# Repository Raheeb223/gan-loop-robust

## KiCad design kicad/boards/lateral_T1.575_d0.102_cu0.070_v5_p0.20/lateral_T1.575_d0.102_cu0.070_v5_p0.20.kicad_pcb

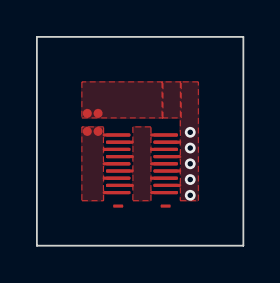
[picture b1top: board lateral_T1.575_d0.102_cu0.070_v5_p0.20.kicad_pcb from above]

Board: 4 copper layers, 11.5 x 11.6 mm, 4 parts (0 on the bottom side), 3 nets.

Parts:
C1, C2: 1uF 0402
Q_S: EPC2015C
Q_T: EPC2015C

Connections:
GND: C1.2, C2.2, Q_S.4, Q_S.6, Q_S.8, Q_S.10
SW: Q_S.3, Q_S.5, Q_S.7, Q_S.9, Q_S.11, Q_T.4, Q_T.6, Q_T.8, Q_T.10
VIN: C1.1, C2.1, Q_T.3, Q_T.5, Q_T.7, Q_T.9, Q_T.11

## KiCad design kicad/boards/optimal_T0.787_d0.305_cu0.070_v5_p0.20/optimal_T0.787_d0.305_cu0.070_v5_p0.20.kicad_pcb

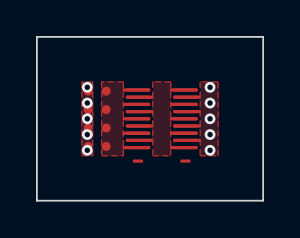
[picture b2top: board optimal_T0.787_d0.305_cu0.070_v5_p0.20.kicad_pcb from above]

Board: 4 copper layers, 12.6 x 9.1 mm, 6 parts (0 on the bottom side), 3 nets.

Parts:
C1, C2, C3, C4: 1uF 0402
Q_S: EPC2015C
Q_T: EPC2015C

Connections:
GND: C1.1, C2.1, C3.1, C4.1, Q_S.4, Q_S.6, Q_S.8, Q_S.10
SW: Q_S.3, Q_S.5, Q_S.7, Q_S.9, Q_S.11, Q_T.4, Q_T.6, Q_T.8, Q_T.10
VIN: C1.2, C2.2, C3.2, C4.2, Q_T.3, Q_T.5, Q_T.7, Q_T.9, Q_T.11

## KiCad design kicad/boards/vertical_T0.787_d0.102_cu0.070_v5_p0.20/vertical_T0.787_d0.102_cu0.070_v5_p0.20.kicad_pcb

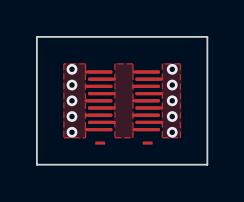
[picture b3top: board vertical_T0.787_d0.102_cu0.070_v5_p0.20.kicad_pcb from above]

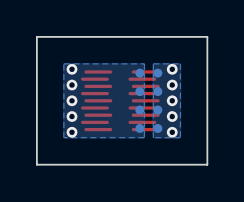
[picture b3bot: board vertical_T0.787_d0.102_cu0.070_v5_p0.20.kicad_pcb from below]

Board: 4 copper layers, 9.5 x 7.1 mm, 6 parts (4 on the bottom side), 3 nets.

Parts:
C1, C2, C3, C4: 1uF 0402
Q_S: EPC2015C
Q_T: EPC2015C

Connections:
GND: C1.2, C2.2, C3.2, C4.2, Q_S.4, Q_S.6, Q_S.8, Q_S.10
SW: Q_S.3, Q_S.5, Q_S.7, Q_S.9, Q_S.11, Q_T.4, Q_T.6, Q_T.8, Q_T.10
VIN: C1.1, C2.1, C3.1, C4.1, Q_T.3, Q_T.5, Q_T.7, Q_T.9, Q_T.11
